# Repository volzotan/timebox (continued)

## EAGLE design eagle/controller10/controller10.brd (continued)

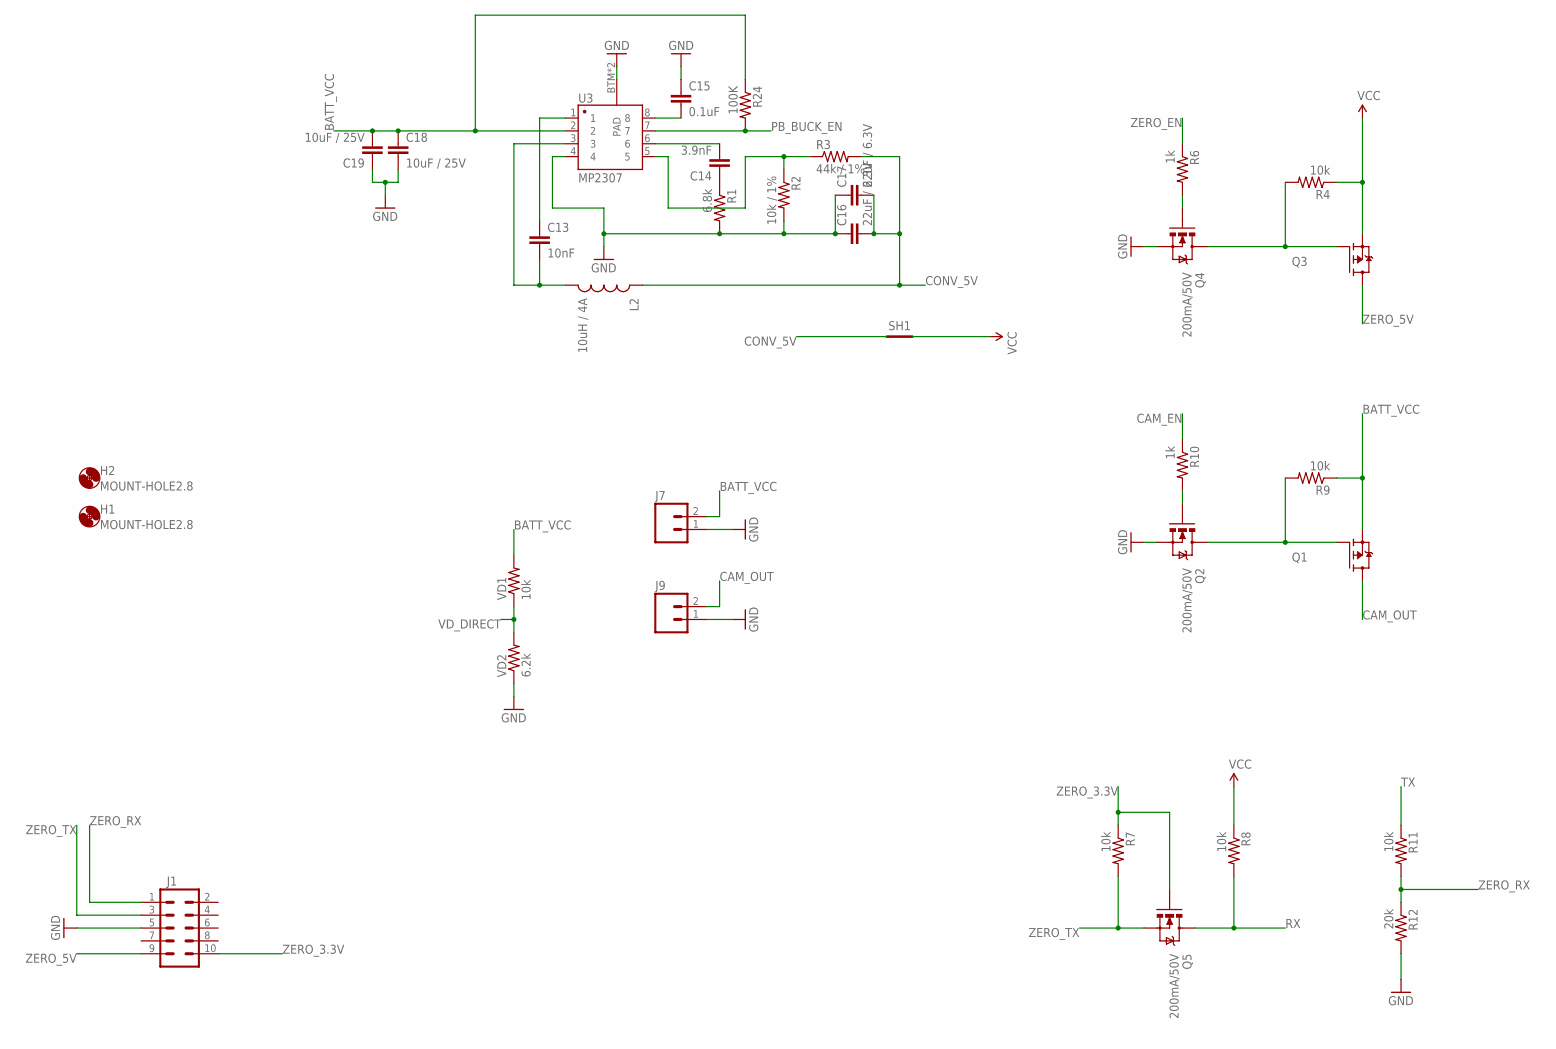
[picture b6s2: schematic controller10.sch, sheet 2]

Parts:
C13: 10nF; 1206
C14: 3.9nF; 0805
C15: 0.1uF; 0805
C16, C17: 22uF / 6.3V; 1210
C18, C19: 10uF / 25V; 1210
H1, H2: MOUNT-HOLE2.8; 2,8
J1: M05X2PTH; AVR_ICSP
J7, J9: M02LOCK; 1X02_LOCK
L2: 10uH / 4A; SRU1038
Q1, Q3: FDD4141TO252; TO252
Q2, Q4, Q5: 200mA/50V; SOT23-3
R1: 6.8k; 0805
R2: 10k / 1%; 0805
R3: 44k / 1%; 0805
R4, R7, R8, R9, R11: 10k; 0805
R6, R10: 1k; 0805
R12: 20k; 0805
R24: 100K; 0805
SH1: SHORT-HT5; SHORT_TOP-50
U3: MP2307; SO08
VD1: 10k; 1206
VD2: 6.2k; 1206

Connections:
BATT_VCC: C18.1, C19.2, J7.2, Q1.2 (S), R9.1, R24.1, U3.2, VD1.2
CAM_EN: R10.1; also elsewhere on the board
CAM_OUT: J9.2, Q1.3 (D)
CONV_5V: C16.2, C17.2, L2.1, R3.2, SH1.1
GND: C15.1, C16.1, C17.1, C18.2, C19.1, J1.5, J7.1, J9.1, Q2.2 (S), Q4.2 (S), R1.2, R2.2, R12.2, U3.4, U3.BTM (PAD), U3.P$1 (PAD), VD2.1; also elsewhere on the board
unnamed: Q1.1 (G), Q2.3 (D), R9.2
unnamed: Q4.1 (G), R6.2
unnamed: Q3.1 (G), Q4.3 (D), R4.2
unnamed: Q2.1 (G), R10.2
unnamed: C15.2, U3.8
unnamed: C13.2, L2.2, U3.3
unnamed: C13.1, U3.1
unnamed: C14.1, R1.1
unnamed: C14.2, U3.6
unnamed: R2.1, R3.1, U3.5
PB_BUCK_EN: R24.2, U3.7
RX: Q5.3 (D), R8.2; also elsewhere on the board
TX: R11.1; also elsewhere on the board
VCC: Q3.2 (S), R4.1, R8.1, SH1.2; also elsewhere on the board
VD_DIRECT: VD1.1, VD2.2; also elsewhere on the board
ZERO_3.3V: J1.10, Q5.1 (G), R7.1
ZERO_5V: J1.9, Q3.3 (D)
ZERO_EN: R6.1; also elsewhere on the board
ZERO_RX: J1.1, R11.2, R12.1
ZERO_TX: J1.3, Q5.2 (S), R7.2

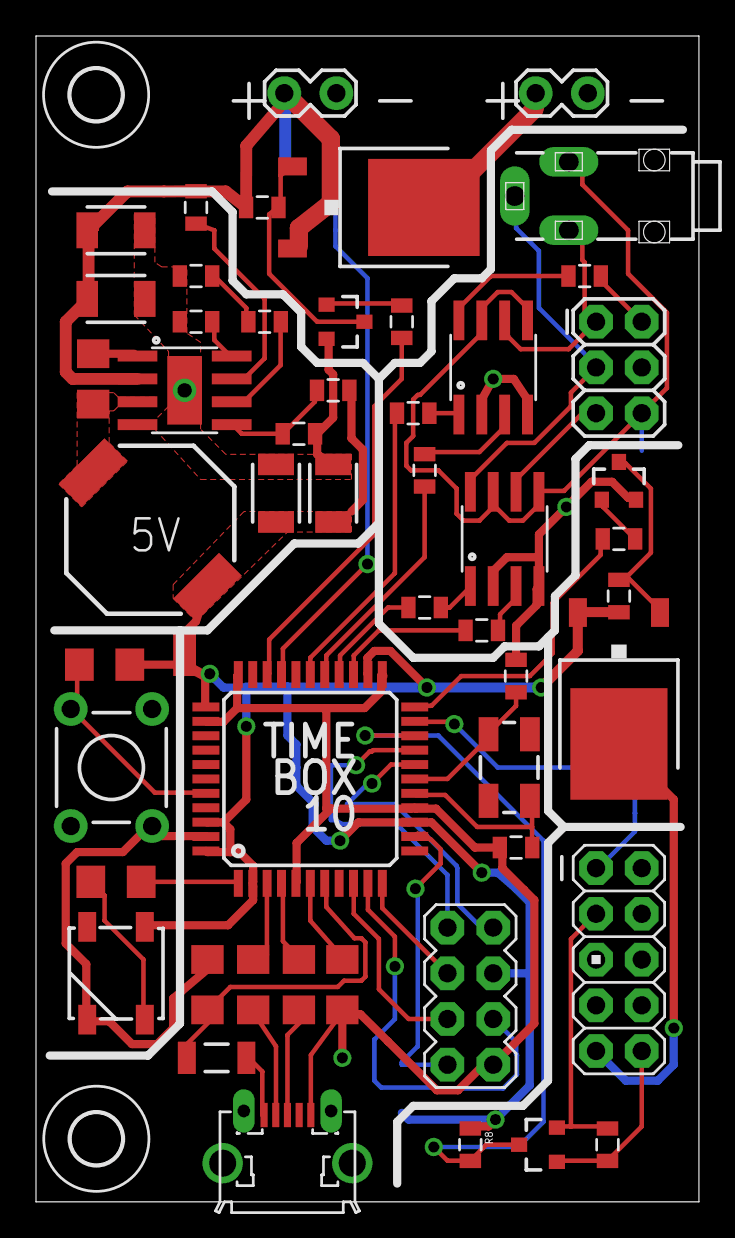
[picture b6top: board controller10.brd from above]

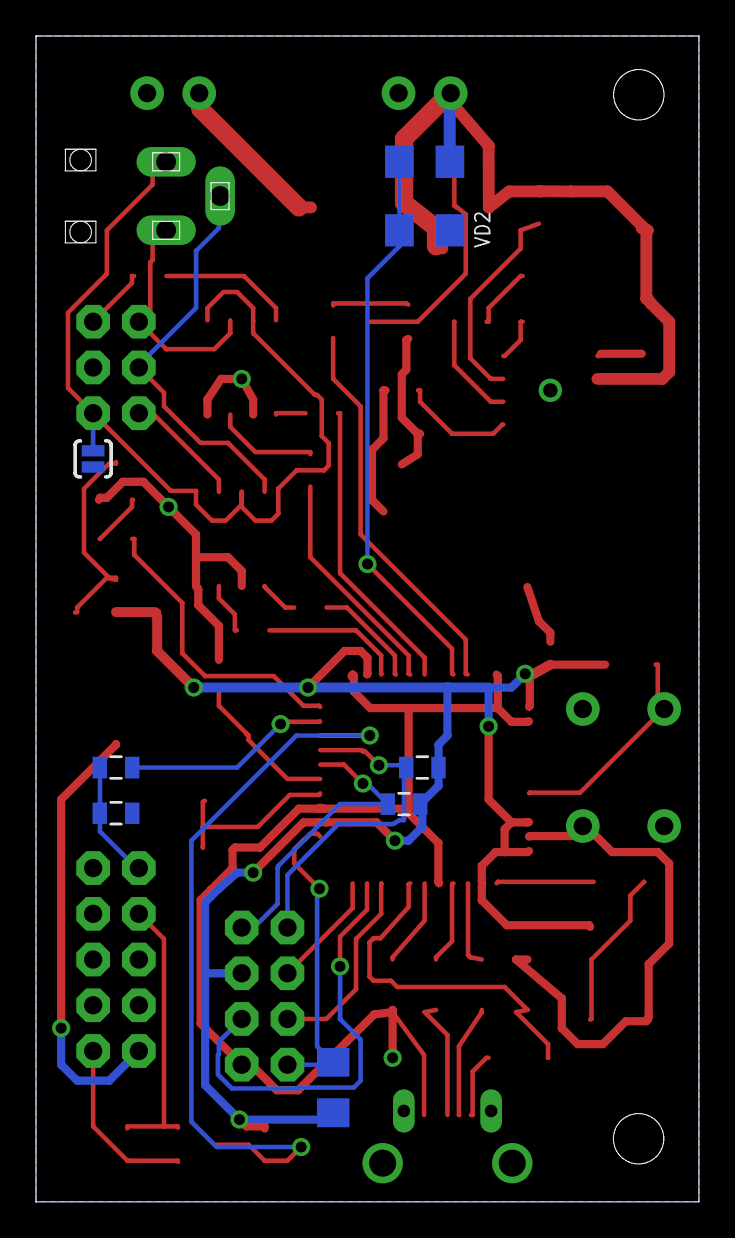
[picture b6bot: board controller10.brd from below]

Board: 2 copper layers, 36.8 x 64.8 mm, 62 parts (8 on the bottom side), 57 nets.
